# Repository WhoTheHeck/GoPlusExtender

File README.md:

# GoPlusExtender

## Idea
The goal of this project is to have the Go Plus modded in a way where it behaves comparable to the simple mod where you solder the vibration motor to the switch. In that simple mod basically everytime you plus would vibrate it will push the button automatically. At the end this results in constant button presses which on one hand drains the battery and on the other hand also always will push the button in events like "catch/spin succesfull", "item bag full", "connection-errors", etc.  
This project aims to react to Go Plus events in a smart way. Only pushing the button when it is necassary. While implementing that there were other convinient features addied like a rechargable LiPo-battery, low battery indicator, manual/automatic mode select, power save functionalities, change to manual catch mode for new pokemon and -very handy- custom vibration motor control! That enables custom vibration patterns which vibrate the motor in automation mode only when e.q. Go Plus disconnects from smartphone, item bag full or pokemon storage full.

## Concept
Hook into LED driving transistors to analize patterns.  
ATTiny45 reads LED signals, processes them, controlls button and vibration motor. Will be in deep sleep when using manual mode

## Partlist
- Battery - ZIPPY 240mAh 20C Single Cell (hobbyking)
- TP4056 Lithium Battery Charger and Protection Module
- PCB components (see BOM in files)
- additional 5.1k 0603 for charge controller PCB --> exchange R3, limits charge current to save limit around 250mA
- 1x 3D printed case top
- 1x 3D printed case bottom
- 1x 3D printed programmer adapter
- 2x PoGo-Pins small (A=4mm, goes in case, for powering GoPlusExtender from battery), (I got them from Aliexpress, Brand TangDa)
- 7x PoGo-Pins long (A=11.5mm, for programmer), (I got them from Aliexpress, Brand(?) TangDa)

## Schematic
find v1 in files  

## Layout
Due to the tiny footprint the PCB had to be done as 4layer board.  
find v1 in files  

## PCB
Necessary components can be found in PCB_BoM.html  
Everything can still be soldered by hand. Using flux is recommended, especially the Analog Switch with the TSSOP-footprint will be trick otherwise.  

## Go Plus Solderpoints & Wiring
Soldering to the LED drivers is the most challenging part, take your time. In that case I recoommend securing the wires with some hot glue (not good practice... I know).  
o Polarity doesn't matter  
W1 --> GoPlusPower+ (from battery connector)  
W2 --> GoPlusPower- (from battery connector)  
W3 --> BatteryPower+ (from BatteryPCB)  
W4 --> BatteryPower- (from BatteryPCB)  
W5 --> switch (from GoPlus upper left)  
W6 --> GoPlus- (where motor was soldered to GoPlus) o  
W7 --> GoPlus+ (where motor was soldered to GoPlus) o  
W8 --> Motor- (desolder from GoPlus, solder here) o  
W9 --> Motor+ (desolder from GoPlus, solder here) o  
W10 --> LED blue (upper IC, upper middle leg)  
W16 --> LED green (lower IC, lower middle leg)  
W18 --> LED red (upper IC, lower middle leg)  
W11,W12,W13,W14,W17 --> Programmer (careful: here correct polarity is important!)  

## Programmer setup
3D printable programmer adapter in files. Needs PoGo-Pins with length = TBD!!!
W11 --> Uno GND
W --> Uno 13 - white
W --> Uno 12 - brown
W --> Uno 11 - purple
W --> Uno 10 - grey
W12 --> Uno 5V

Set mode to manuel when reprogramming!  
Search online for instructions to use Arduino Uno as programmer for ATTinys.

## Assembly

- 3D print case
- add PoGo-Pins to Case, position might needs to be adjusted a little by heating while soldering (needs case-rework)
- solder wires to ChargePCB
- wrap battery in isolation/kapton tape
(change ChargePCB current resistor to xxx ohms)
- attach battery to charge-PCB as seen in pictures
- put battery unit in bottom part, PCB will snapfit in place
- liftup battery, solder wires to PoGo-Pins

- desolder motor from GoPlus
- solder wires to GoPlus as shown above
- solder GoPlus-ExtenderPCB
- add motor
- solder wires to GoPlus as shown above
- put GoPlus push-button and silicon rubber in top case

- put ExtenderPCB+GoPlus in top case, screw GoPlus in place
- put motor in bottom case, use foam to dampen vibrations, maybe add soft glue to hold in place

## Codebase

### Special variables
SIMULATING --> uncomment for checking code in Atmel Studio. Delays certain actions and skips EEPROM access.  
DEBUGING --> uncomment for upload to ATTiny with debug LED. Error LED will also light up when button gets pressed automatically.

### Main function
main():  
- defines input/output pins  
- defines interrupts  
	- input interrupt monitors LED patterns  
	- timer interrupt gets battery voltage every our (also whenever you power it up)  

### LED analizer functions
BlueHandle()  
GreenHandle()  
RedHandle()  
WhiteHandle()  
YellowHandle()  
- If the corresponding transistors get controlled the inputs at the ATTiny get pulled high, this enables interrupt-routine.  
WaitCount()  
- Counts how often function gets called, button gets pushed after ~30sec of idling to counteract a situation where GoPlus does not react to new Pokemon or Pokestops until useraction occures.  
TrackReset()  
- Reset the counted LED state after initalization or if no new LED-state has been detected for 30sec.  

### Randomized wait functions
This aims to make button presses more human like. There wont be any need to use this, but it's a nice savety feature.  
  
GetSeed()  
- Get & update seed value for randomized reactions.  
MyRandGet() 
- Generate new random-value. Initially based on seed.  
WaitRand()  
- Delay action by randomized time in ms.  

### Switch and motor control functions
SwitchFunc()  
- Controlles switch presses.
MotorFunc()  
- Controlles rumbling motor dependent on auto or manual mode.

### Power save / deep sleep functions
goToSleep()  
- Deep sleep ATTiny to save power.  
adc_init()  
- Enable ADC. Used to measure battery voltage.  
adc_disable()  
- Disable ADC after measurement to save power.  

### Battery monitoring functions
batt_meas()  
- Measure battery voltage.  
batt_state()  
- Read measured voltage. Enable low-battery-LED in 3.1 .. 3.2V range. LED will be disable at lower voltages to avoid additional battery drain.  

## Appendix

### Simulation
Attached in files is the simulation file that can be used with LTSpice. It shows how the PWM pulsed signal of the LED drivers gets smoothed and reduced by the diode and resistor divider to then be read by the ATTiny as a compatible digital input.  

### GoPlus Model
Files contain derived GoPlus model usable as reference for modeling.

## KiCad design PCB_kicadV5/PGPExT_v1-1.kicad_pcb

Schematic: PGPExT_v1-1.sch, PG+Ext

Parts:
C1: 22n; C_0805_2012Metric
C2: 100n; C_0805_2012Metric
C3: 4.7u; CP_Elec_4x5.3
D1: D_ALT; D_SOT-23_ANK
JP1: Jumper_NO_Small; SolderJumper-2_P1.3mm_Open_RoundedPad1.0x1.5mm
R1: 2k7; R_0603_1608Metric
SW1: SW_SPDT; SW_SSSS912500_ALPS
U1: TS5A3166; SOT-23-5
U2: TC1271A; SOT-23-5
U3: SN74AUC1GU; SOT-23-5
U4: TPS22918; SOT-23-6
U5: ADG888YRUZ; TSSOP-16_4.4x5mm_P0.65mm
U6: TPS76930; SOT-23-5
W1: GoPlusPower+; TestPoint_Pad_D1.5mm
W2: GoPlusPower-; TestPoint_Pad_D1.5mm
W3: BatteryPower+; TestPoint_Pad_D1.5mm
W4: BatteryPower-; TestPoint_Pad_D1.5mm
W5: switch; TestPoint_Pad_D1.5mm
W6: GoPlus-; TestPoint_Pad_D1.5mm
W7: GoPlus+; TestPoint_Pad_D1.5mm
W8: motor-; TestPoint_Pad_D1.5mm
W9: motor+; TestPoint_Pad_D1.5mm

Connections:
+BATT: U2.2, U3.5, U4.1, W3.1; also elsewhere on the board
/mode_select: SW1.2; also elsewhere on the board
/motor_auto: U5.9; also elsewhere on the board
/motor_manual: U5.8; also elsewhere on the board
/switch: R1.2; also elsewhere on the board
GND: C1.2, C2.2, C3.2, JP1.2, SW1.3, U1.2, U1.3, U2.5, U3.3, U4.2, U5.14, U5.16, U6.2 (GND), W2.1, W4.1; also elsewhere on the board
unnamed: C1.1, U3.4, U4.3
unnamed: D1.1, U5.4, U5.10, W9.1
unnamed: D1.2, U5.5, U5.15, W8.1
unnamed: JP1.1, U2.3
unnamed: R1.1, U1.4
unnamed: U1.1, W5.1
unnamed: U2.4, U3.2, U6.3 (~EN~)
unnamed: U5.3, W7.1
unnamed: U5.6, W6.1
VDD: C2.1, C3.1, U1.5, U5.1, U5.11, U6.5 (OUT), W1.1; also elsewhere on the board
VDDA: U4.6, U6.1 (IN)

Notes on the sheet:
+ 5kR 0603 for charge controller
charge controller
connect right pads to vib-motor connect left pads to GoPlus
connect to switch plus (top) of GoPlus
Connection for GoPlus
Automation mode selector
Vibration motor control
Button pressing switch
Power management
3.0V!
Pokemon Go Plus Extender v1.0
3,08V shutoff
manuel auto
Connection for battery

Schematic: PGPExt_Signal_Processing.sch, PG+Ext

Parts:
C4, C6, C7: 47n; C_0805_2012Metric
C5: 100n; C_0805_2012Metric
D2, D4: D_Schottky_Dual; SOT-343_SC-70-4
D3: LED_red; LED_0805_2012Metric
D5: LED_ora; LED_0805_2012Metric
R2: 470k; R_0603_1608Metric
R3: 1Meg; R_0603_1608Metric
R4, R7, R11: 1k; R_0603_1608Metric
R5, R8, R12: 10k; R_0603_1608Metric
R6, R9, R13: 100k; R_0603_1608Metric
R10, R14: 220; R_0603_1608Metric
U7: ATTINY44A-SSU; SOIC-14_3.9x8.7mm_P1.27mm
W10: LEDb_i; TestPoint_Pad_D1.5mm
W11: program-; TestPoint_Pad_D1.5mm
W12: program+; TestPoint_Pad_D1.5mm
W13, W14, W15, W17: TEST_1P; TestPoint_Pad_D1.5mm
W16: LEDg_i; TestPoint_Pad_D1.5mm
W18: LEDr_i; TestPoint_Pad_D1.5mm

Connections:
+BATT: R2.2; also elsewhere on the board
/PGPExt_Signal_Processing/LEDb: R5.2, R6.1, U7.12 (PA1)
/PGPExt_Signal_Processing/LEDb_i: R4.2, W10.1
/PGPExt_Signal_Processing/LEDg: R8.2, R9.1, U7.11 (PA2)
/PGPExt_Signal_Processing/LEDg_i: R7.2, W16.1
/PGPExt_Signal_Processing/LEDr: R12.2, R13.1, U7.10 (PA3)
/PGPExt_Signal_Processing/LEDr_i: R11.2, W18.1
/PGPExt_Signal_Processing/battvolt: R2.1, R3.2, U7.6 (PA7)
/mode_select: U7.5 (PB2); also elsewhere on the board
/motor_auto: U7.3 (XTAL2/PB1); also elsewhere on the board
/motor_manual: U7.2 (XTAL1/PB0); also elsewhere on the board
/switch: U7.13 (AREF/PA0); also elsewhere on the board
GND: C4.2, C5.2, C6.2, C7.2, D3.1, D5.1, R3.1, R6.2, R9.2, R13.2, U7.14 (GND), W11.1; also elsewhere on the board
unnamed: C4.1, D2.1, R5.1
unnamed: C6.1, D2.4, R8.1
unnamed: C7.1, D4.1, R12.1
unnamed: D2.2, R4.1
unnamed: D2.3, R7.1
unnamed: D3.2, R10.1
unnamed: D4.2, R11.1
unnamed: D5.2, R14.1
unnamed: R10.2, U7.8 (PA5), W14.1
unnamed: R14.2, U7.7 (PA6), W17.1
unnamed: U7.4 (~RESET~/PB3), W15.1
unnamed: U7.9 (PA4), W13.1
VDD: C5.1, U7.1 (VCC), W12.1; also elsewhere on the board

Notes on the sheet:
LEDb - in LEDg - in LEDr - in motor_manual - out motor_auto - out switch - out mode select - in w/ internal pullup
orange LED for error occurences
maybe use 82k instead of 100k to not get more than 3V high
Attiny44A
LED input with PWM smoothing
set mode=manuel when reprogramming!

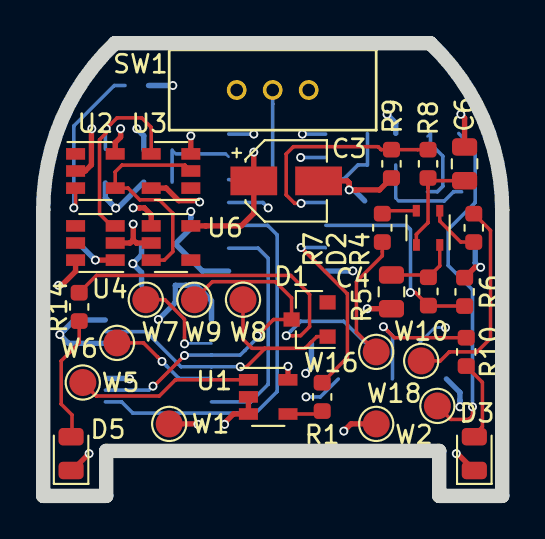
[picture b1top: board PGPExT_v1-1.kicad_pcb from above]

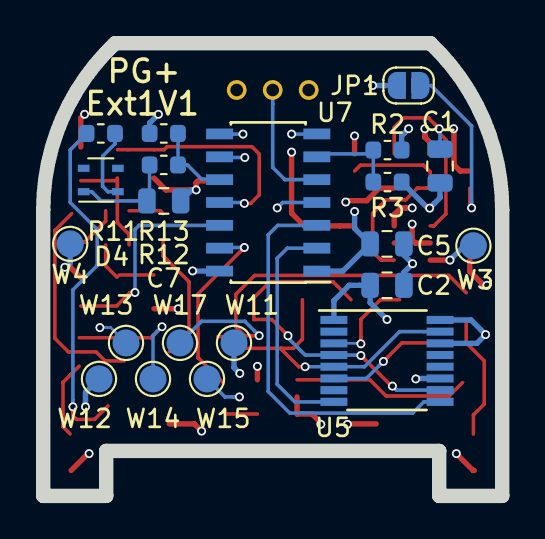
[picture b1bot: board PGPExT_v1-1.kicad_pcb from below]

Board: 4 copper layers, 25.5 x 25.2 mm, 53 parts (21 on the bottom side), 36 nets.

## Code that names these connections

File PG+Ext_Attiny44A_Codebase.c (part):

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
ISR(PCINT0_vect)
{
    if (PINA & (1<<PINA1) )                                 //ledb
        LED_state_n |= (1<<0);
    else LED_state_n &= ~(1<<0);
    if (PINA & (1<<PINA2) )                                 //ledg
        LED_state_n |= (1<<1);
    else LED_state_n &= ~(1<<1);
    if (PINA & (1<<PINA3) )                                 //ledr
        LED_state_n |= (1<<2);
    else LED_state_n &= ~(1<<2);

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
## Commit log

2019-03-10 Add files via upload
    initial versions
2019-11-15 change to propper codebase
    correct pin assignment
    includes debugging mode & battery monitoring
2019-11-15 pdf of PCB layout
    v1.1 fixes a bug with diode pin assignment
2019-11-15 update to 1.1
    fixing diode pin assignment and routing
2020-05-01 Added Gerber-Files
    added Gerber-files for manufacturers that don't import KiCAD files
    removed old/faulty PCB version
2020-05-01 updated readme
    test picture upload
2020-05-01 fix images
2020-05-02 Create LICENSE
2020-05-02 add demo video
2020-05-02 update video link
2020-05-04 readme addup
